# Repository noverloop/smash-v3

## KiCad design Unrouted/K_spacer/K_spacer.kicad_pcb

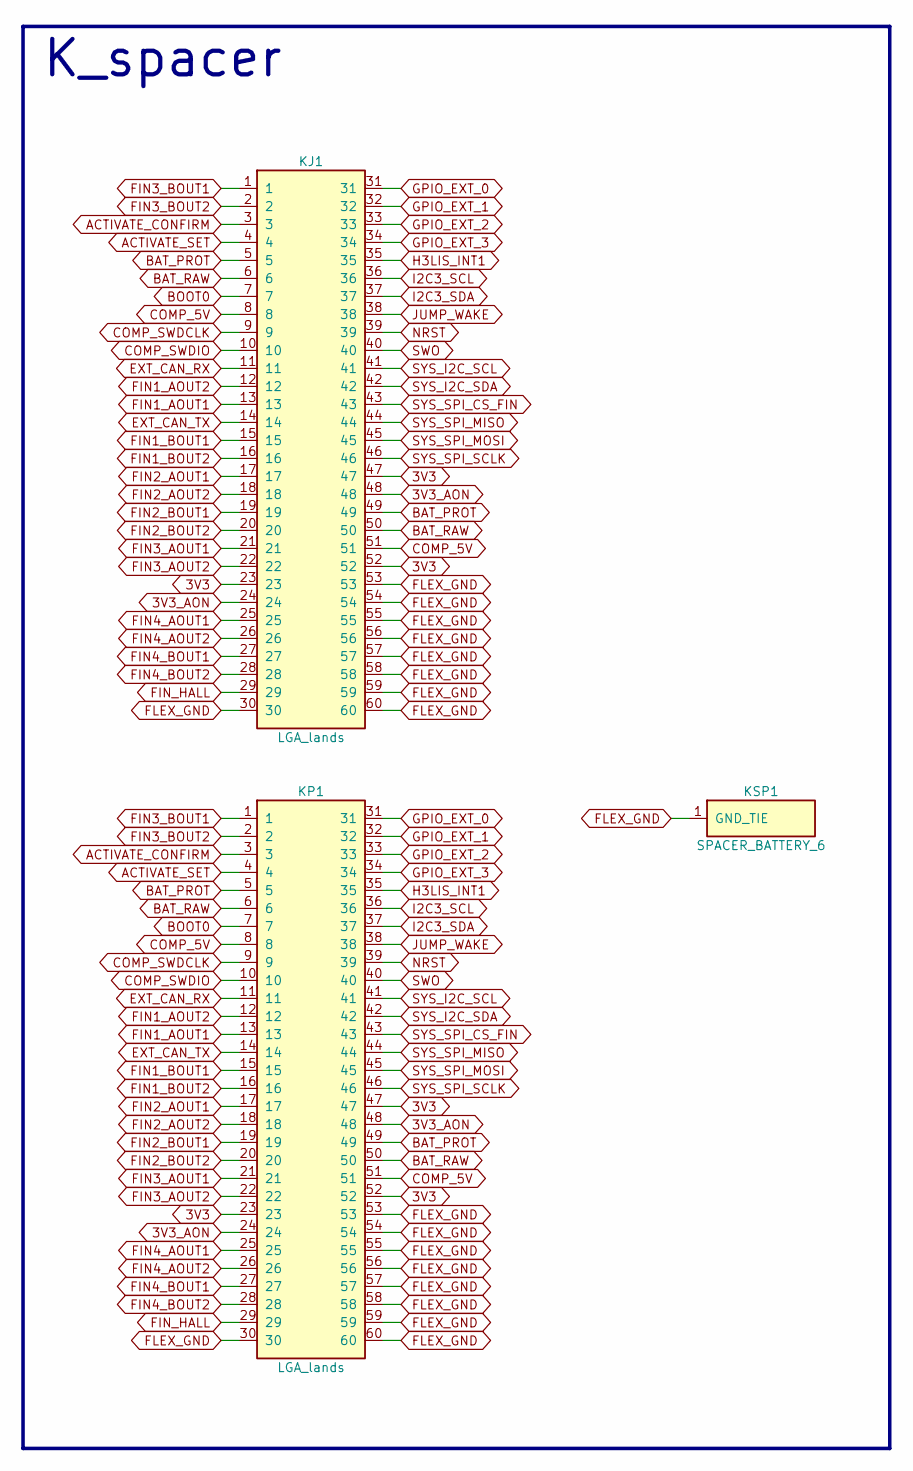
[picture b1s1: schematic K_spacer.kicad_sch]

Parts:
KJ1: LGA_lands; J_spacer_battery_6_top; MPN LGA_lands
KP1: LGA_lands; P_spacer_battery_6_bot; MPN LGA_lands
KSP1: SPACER_BATTERY_6; Spacer_Mechanical_34mm

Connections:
3V3: KJ1.23, KJ1.47, KJ1.52, KP1.23, KP1.47, KP1.52
3V3_AON: KJ1.24, KJ1.48, KP1.24, KP1.48
ACTIVATE_CONFIRM: KJ1.3, KP1.3
ACTIVATE_SET: KJ1.4, KP1.4
BAT_PROT: KJ1.5, KJ1.49, KP1.5, KP1.49
BAT_RAW: KJ1.6, KJ1.50, KP1.6, KP1.50
BOOT0: KJ1.7, KP1.7
COMP_5V: KJ1.8, KJ1.51, KP1.8, KP1.51
COMP_SWDCLK: KJ1.9, KP1.9
COMP_SWDIO: KJ1.10, KP1.10
EXT_CAN_RX: KJ1.11, KP1.11
EXT_CAN_TX: KJ1.14, KP1.14
FIN1_AOUT1: KJ1.13, KP1.13
FIN1_AOUT2: KJ1.12, KP1.12
FIN1_BOUT1: KJ1.15, KP1.15
FIN1_BOUT2: KJ1.16, KP1.16
FIN2_AOUT1: KJ1.17, KP1.17
FIN2_AOUT2: KJ1.18, KP1.18
FIN2_BOUT1: KJ1.19, KP1.19
FIN2_BOUT2: KJ1.20, KP1.20
FIN3_AOUT1: KJ1.21, KP1.21
FIN3_AOUT2: KJ1.22, KP1.22
FIN3_BOUT1: KJ1.1, KP1.1
FIN3_BOUT2: KJ1.2, KP1.2
FIN4_AOUT1: KJ1.25, KP1.25
FIN4_AOUT2: KJ1.26, KP1.26
FIN4_BOUT1: KJ1.27, KP1.27
FIN4_BOUT2: KJ1.28, KP1.28
FIN_HALL: KJ1.29, KP1.29
FLEX_GND: KJ1.30, KJ1.53, KJ1.54, KJ1.55, KJ1.56, KJ1.57, KJ1.58, KJ1.59, KJ1.60, KP1.30, KP1.53, KP1.54, KP1.55, KP1.56, KP1.57, KP1.58, KP1.59, KP1.60, KSP1.1
GPIO_EXT_0: KJ1.31, KP1.31
GPIO_EXT_1: KJ1.32, KP1.32
GPIO_EXT_2: KJ1.33, KP1.33
GPIO_EXT_3: KJ1.34, KP1.34
H3LIS_INT1: KJ1.35, KP1.35
I2C3_SCL: KJ1.36, KP1.36
I2C3_SDA: KJ1.37, KP1.37
JUMP_WAKE: KJ1.38, KP1.38
NRST: KJ1.39, KP1.39
SWO: KJ1.40, KP1.40
SYS_I2C_SCL: KJ1.41, KP1.41
SYS_I2C_SDA: KJ1.42, KP1.42
SYS_SPI_CS_FIN: KJ1.43, KP1.43
SYS_SPI_MISO: KJ1.44, KP1.44
SYS_SPI_MOSI: KJ1.45, KP1.45
SYS_SPI_SCLK: KJ1.46, KP1.46

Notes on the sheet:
K_spacer

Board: 2 copper layers, 4 parts (1 on the bottom side), 46 nets, no tracks yet.

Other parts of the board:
KMH1: smash_mech_potting

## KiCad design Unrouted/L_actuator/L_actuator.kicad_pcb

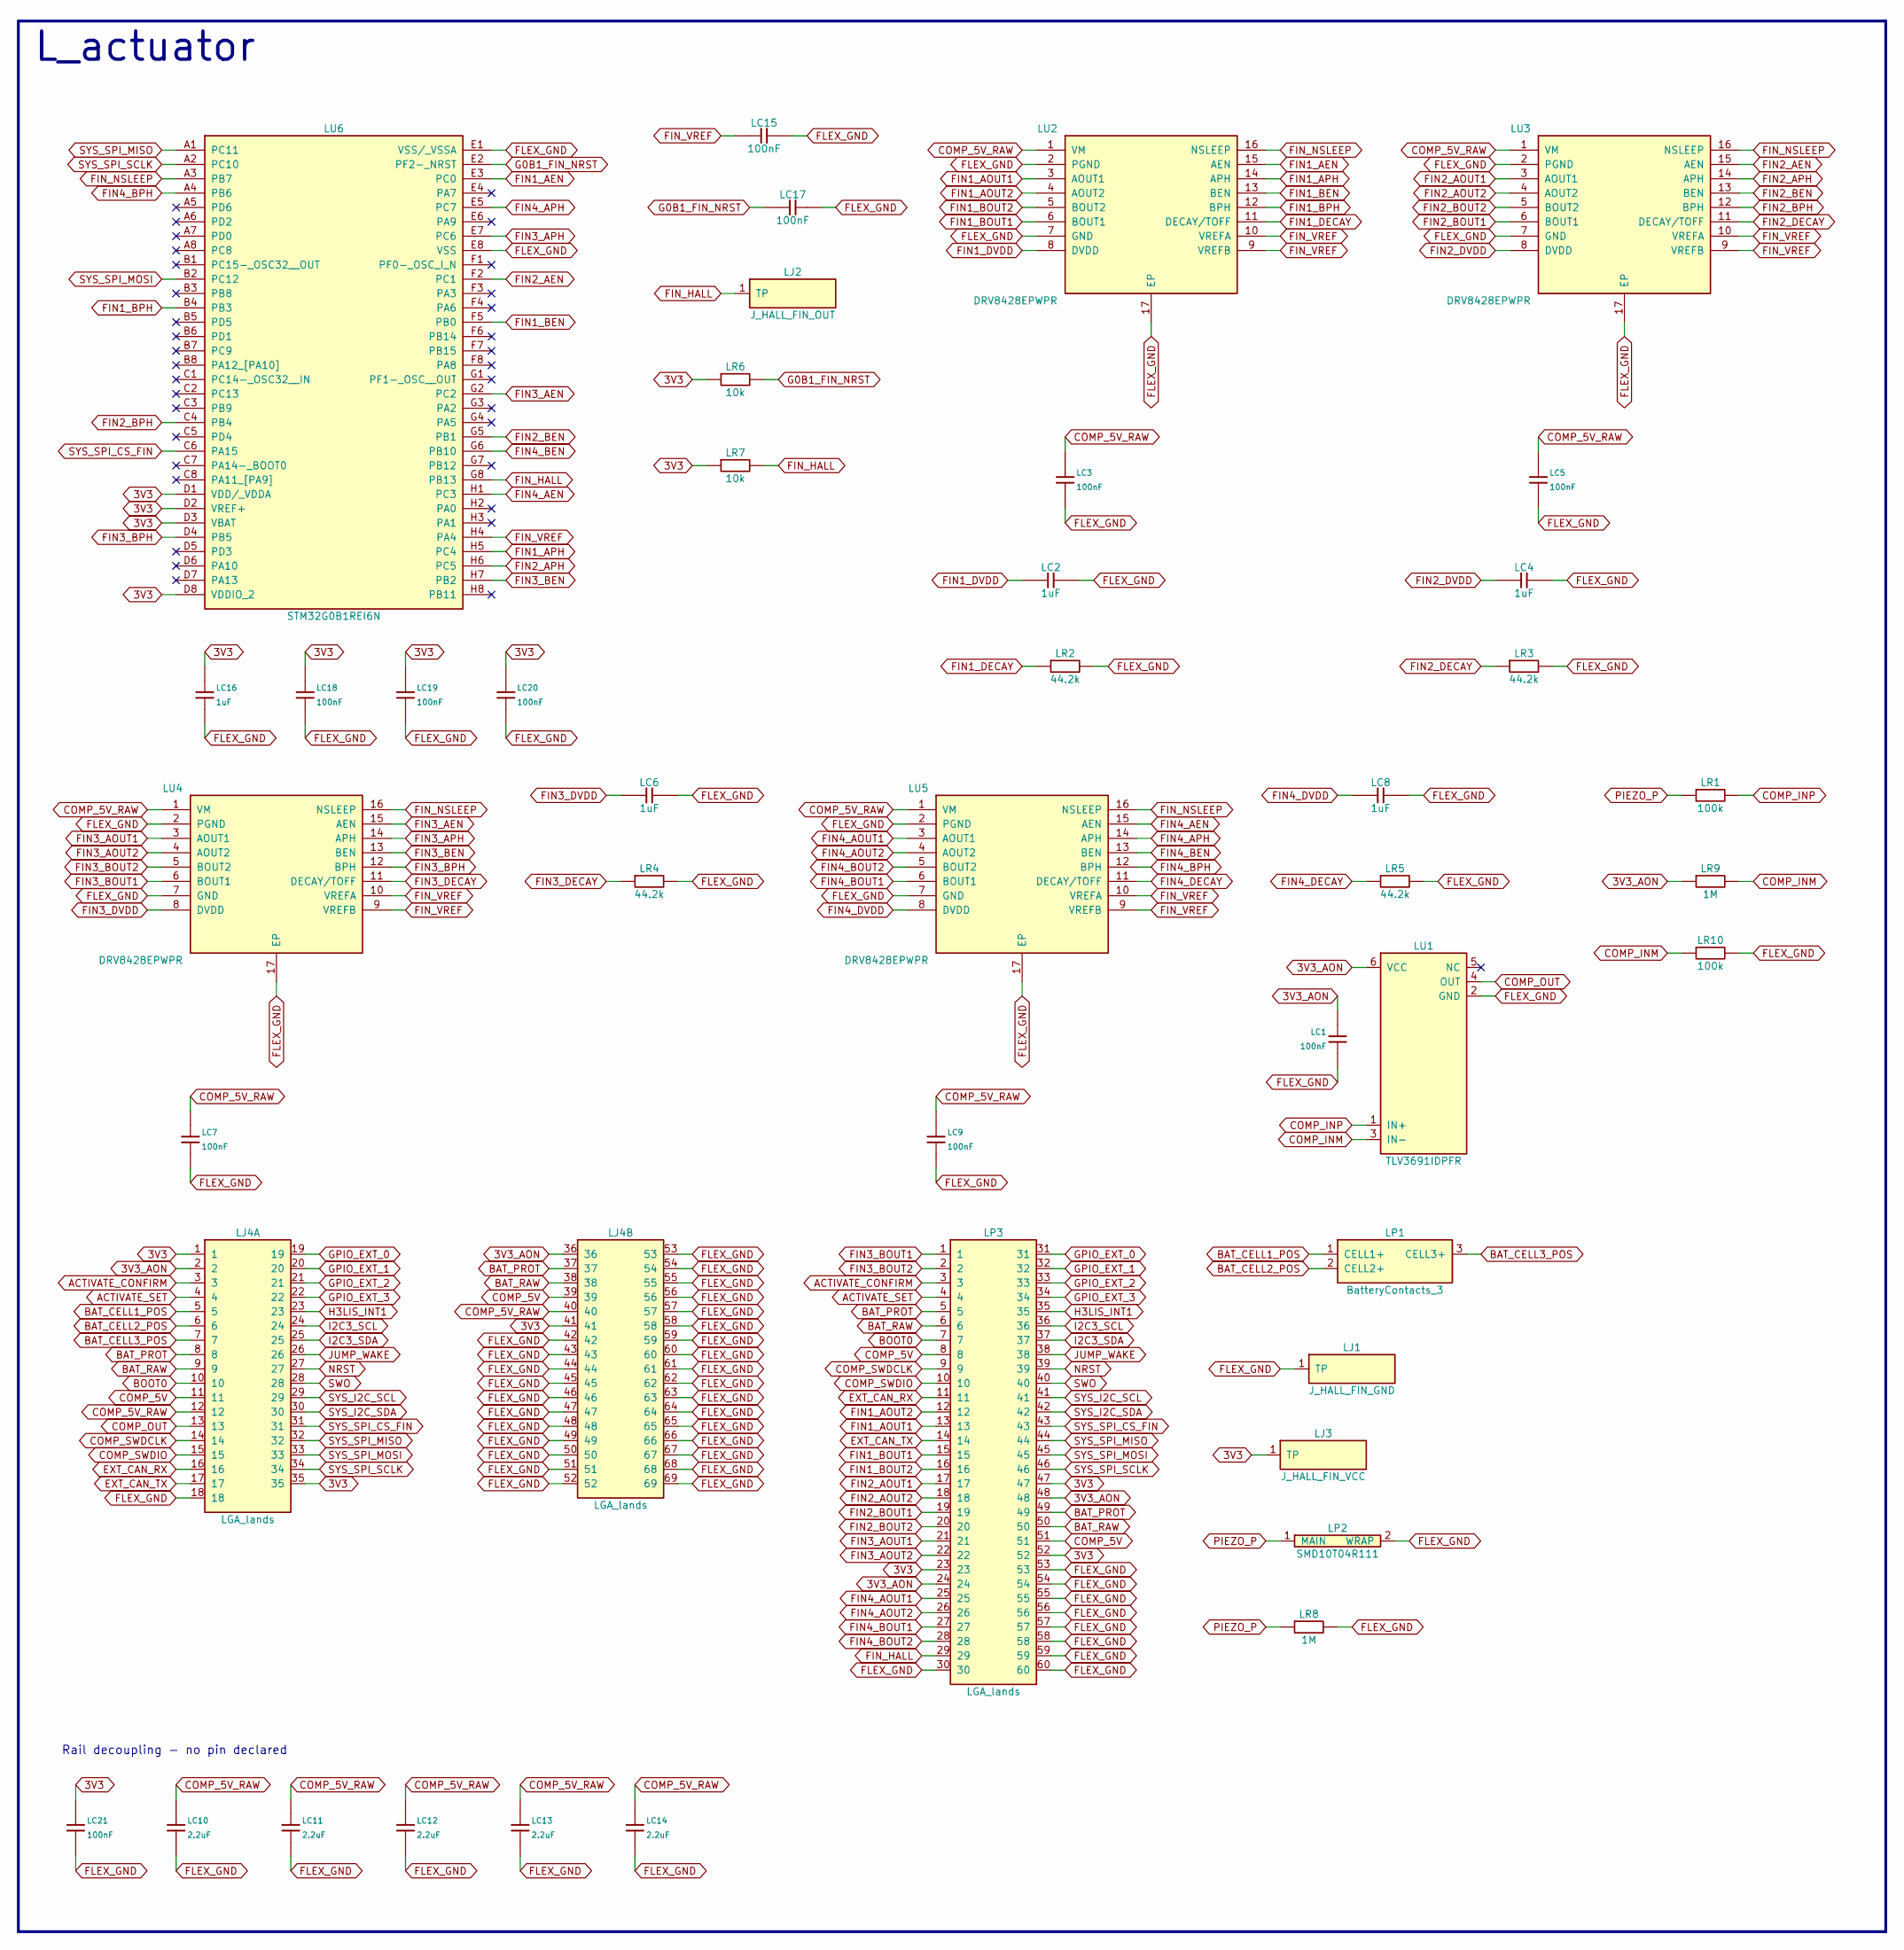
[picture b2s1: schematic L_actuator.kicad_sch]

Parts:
LC1, LC3, LC5, LC7, LC9, LC15, LC17, LC18, LC19, LC20, LC21: 100nF; Capacitor_SMD_C_0402_1005Metric; MPN C0402 X7R 100nF
LC2, LC4, LC6, LC8, LC16: 1uF; Capacitor_SMD_C_0805_2012Metric; MPN C-Series MIL-PRF-32535 X7R 0805 1uF
LC10, LC11, LC12, LC13, LC14: 2.2uF; Capacitor_SMD_C_0603_1608Metric; MPN C-Series MIL-PRF-32535 X7R 0603 2.2uF
LJ1: J_HALL_FIN_GND; Pogo_Pad_D2.0mm
LJ2: J_HALL_FIN_OUT; Pogo_Pad_D2.0mm
LJ3: J_HALL_FIN_VCC; Pogo_Pad_D2.0mm
LJ4: LGA_lands; J_fin_ble_board_spacer_fin_ble_board_wakeup_board; MPN LGA_lands
LP1: BatteryContacts_3; MPN BatteryContacts_3
LP2: SMD10T04R111; PiezoDisc_SMD10T04R111; MPN SMD10T04R111
LP3: LGA_lands; P_fin_ble_board_spacer_battery_6; MPN LGA_lands
LR1, LR10: 100k; Resistor_SMD_R_0402_1005Metric; MPN CRCW0402 100k 1% e3
LR2, LR3, LR4, LR5: 44.2k; Resistor_SMD_R_0402_1005Metric; MPN CRCW0402 44.2k 1% e3
LR6, LR7: 10k; Resistor_SMD_R_0402_1005Metric; MPN CRCW0402 10k 1% e3
LR8, LR9: 1M; Resistor_SMD_R_0402_1005Metric; MPN CRCW0402 1M 1% e3
LU1: TLV3691IDPFR; DPF0006A; MPN TLV3691IDPFR
LU2, LU3, LU4, LU5: DRV8428EPWPR; SOP65P640X120-17N; MPN DRV8428EPWPR
LU6: STM32G0B1REI6N; BGA64C50P8X8_500X500X60; MPN STM32G0B1REI6N

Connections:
3V3: LC16.1, LC18.1, LC19.1, LC20.1, LC21.1, LJ3.1, LJ4.1, LJ4.35, LJ4.41, LP3.23, LP3.47, LP3.52, LR6.1, LR7.1, LU6.D1 (VDD/_VDDA), LU6.D2 (VREF+), LU6.D3 (VBAT), LU6.D8 (VDDIO_2)
3V3_AON: LC1.1, LJ4.2, LJ4.36, LP3.24, LP3.48, LR9.1, LU1.6 (VCC)
ACTIVATE_CONFIRM: LJ4.3, LP3.3
ACTIVATE_SET: LJ4.4, LP3.4
BAT_CELL1_POS: LJ4.5, LP1.1 (CELL1+)
BAT_CELL2_POS: LJ4.6, LP1.2 (CELL2+)
BAT_CELL3_POS: LJ4.7, LP1.3 (CELL3+)
BAT_PROT: LJ4.8, LJ4.37, LP3.5, LP3.49
BAT_RAW: LJ4.9, LJ4.38, LP3.6, LP3.50
BOOT0: LJ4.10, LP3.7
COMP_5V: LJ4.11, LJ4.39, LP3.8, LP3.51
COMP_5V_RAW: LC3.1, LC5.1, LC7.1, LC9.1, LC10.1, LC11.1, LC12.1, LC13.1, LC14.1, LJ4.12, LJ4.40, LU2.1 (VM), LU3.1 (VM), LU4.1 (VM), LU5.1 (VM)
COMP_INM: LR9.2, LR10.1, LU1.3 (IN-)
COMP_INP: LR1.2, LU1.1 (IN+)
COMP_OUT: LJ4.13, LU1.4 (OUT)
COMP_SWDCLK: LJ4.14, LP3.9
COMP_SWDIO: LJ4.15, LP3.10
EXT_CAN_RX: LJ4.16, LP3.11
EXT_CAN_TX: LJ4.17, LP3.14
FIN1_AEN: LU2.15 (AEN), LU6.E3 (PC0)
FIN1_AOUT1: LP3.13, LU2.3 (AOUT1)
FIN1_AOUT2: LP3.12, LU2.4 (AOUT2)
FIN1_APH: LU2.14 (APH), LU6.H5 (PC4)
FIN1_BEN: LU2.13 (BEN), LU6.F5 (PB0)
FIN1_BOUT1: LP3.15, LU2.6 (BOUT1)
FIN1_BOUT2: LP3.16, LU2.5 (BOUT2)
FIN1_BPH: LU2.12 (BPH), LU6.B4 (PB3)
FIN1_DECAY: LR2.1, LU2.11 (DECAY/TOFF)
FIN1_DVDD: LC2.1, LU2.8 (DVDD)
FIN2_AEN: LU3.15 (AEN), LU6.F2 (PC1)
FIN2_AOUT1: LP3.17, LU3.3 (AOUT1)
FIN2_AOUT2: LP3.18, LU3.4 (AOUT2)
FIN2_APH: LU3.14 (APH), LU6.H6 (PC5)
FIN2_BEN: LU3.13 (BEN), LU6.G5 (PB1)
FIN2_BOUT1: LP3.19, LU3.6 (BOUT1)
FIN2_BOUT2: LP3.20, LU3.5 (BOUT2)
FIN2_BPH: LU3.12 (BPH), LU6.C4 (PB4)
FIN2_DECAY: LR3.1, LU3.11 (DECAY/TOFF)
FIN2_DVDD: LC4.1, LU3.8 (DVDD)
FIN3_AEN: LU4.15 (AEN), LU6.G2 (PC2)
FIN3_AOUT1: LP3.21, LU4.3 (AOUT1)
FIN3_AOUT2: LP3.22, LU4.4 (AOUT2)
FIN3_APH: LU4.14 (APH), LU6.E7 (PC6)
FIN3_BEN: LU4.13 (BEN), LU6.H7 (PB2)
FIN3_BOUT1: LP3.1, LU4.6 (BOUT1)
FIN3_BOUT2: LP3.2, LU4.5 (BOUT2)
FIN3_BPH: LU4.12 (BPH), LU6.D4 (PB5)
FIN3_DECAY: LR4.1, LU4.11 (DECAY/TOFF)
FIN3_DVDD: LC6.1, LU4.8 (DVDD)
FIN4_AEN: LU5.15 (AEN), LU6.H1 (PC3)
FIN4_AOUT1: LP3.25, LU5.3 (AOUT1)
FIN4_AOUT2: LP3.26, LU5.4 (AOUT2)
FIN4_APH: LU5.14 (APH), LU6.E5 (PC7)
FIN4_BEN: LU5.13 (BEN), LU6.G6 (PB10)
FIN4_BOUT1: LP3.27, LU5.6 (BOUT1)
FIN4_BOUT2: LP3.28, LU5.5 (BOUT2)
FIN4_BPH: LU5.12 (BPH), LU6.A4 (PB6)
FIN4_DECAY: LR5.1, LU5.11 (DECAY/TOFF)
FIN4_DVDD: LC8.1, LU5.8 (DVDD)
FIN_HALL: LJ2.1, LP3.29, LR7.2, LU6.G8 (PB13)
FIN_NSLEEP: LU2.16 (NSLEEP), LU3.16 (NSLEEP), LU4.16 (NSLEEP), LU5.16 (NSLEEP), LU6.A3 (PB7)
FIN_VREF: LC15.1, LU2.9 (VREFB), LU2.10 (VREFA), LU3.9 (VREFB), LU3.10 (VREFA), LU4.9 (VREFB), LU4.10 (VREFA), LU5.9 (VREFB), LU5.10 (VREFA), LU6.H4 (PA4)
FLEX_GND: LC1.2, LC2.2, LC3.2, LC4.2, LC5.2, LC6.2, LC7.2, LC8.2, LC9.2, LC10.2, LC11.2, LC12.2, LC13.2, LC14.2, LC15.2, LC16.2, LC17.2, LC18.2, LC19.2, LC20.2, LC21.2, LJ1.1, LJ4.18, LJ4.42, LJ4.43, LJ4.44, LJ4.45, LJ4.46, LJ4.47, LJ4.48, LJ4.49, LJ4.50, LJ4.51, LJ4.52, LJ4.53, LJ4.54, LJ4.55, LJ4.56, LJ4.57, LJ4.58, LJ4.59, LJ4.60, LJ4.61, LJ4.62, LJ4.63, LJ4.64, LJ4.65, LJ4.66, LJ4.67, LJ4.68, LJ4.69, LP2.2 (WRAP), LP3.30, LP3.53, LP3.54, LP3.55, LP3.56, LP3.57, LP3.58, LP3.59, LP3.60, LR2.2, LR3.2, LR4.2, LR5.2, LR8.2, LR10.2, LU1.2 (GND), LU2.2 (PGND), LU2.7 (GND), LU2.17 (EP), LU3.2 (PGND), LU3.7 (GND), LU3.17 (EP), LU4.2 (PGND), LU4.7 (GND), LU4.17 (EP), LU5.2 (PGND), LU5.7 (GND), LU5.17 (EP), LU6.E1 (VSS/_VSSA), LU6.E8 (VSS)
G0B1_FIN_NRST: LC17.1, LR6.2, LU6.E2 (PF2-_NRST)
GPIO_EXT_0: LJ4.19, LP3.31
GPIO_EXT_1: LJ4.20, LP3.32
GPIO_EXT_2: LJ4.21, LP3.33
GPIO_EXT_3: LJ4.22, LP3.34
H3LIS_INT1: LJ4.23, LP3.35
I2C3_SCL: LJ4.24, LP3.36
I2C3_SDA: LJ4.25, LP3.37
JUMP_WAKE: LJ4.26, LP3.38
NRST: LJ4.27, LP3.39
PIEZO_P: LP2.1 (MAIN), LR1.1, LR8.1
SWO: LJ4.28, LP3.40
SYS_I2C_SCL: LJ4.29, LP3.41
SYS_I2C_SDA: LJ4.30, LP3.42
SYS_SPI_CS_FIN: LJ4.31, LP3.43, LU6.C6 (PA15)
SYS_SPI_MISO: LJ4.32, LP3.44, LU6.A1 (PC11)
SYS_SPI_MOSI: LJ4.33, LP3.45, LU6.B2 (PC12)
SYS_SPI_SCLK: LJ4.34, LP3.46, LU6.A2 (PC10)

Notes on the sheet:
L_actuator
Rail decoupling - no pin declared

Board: 14 copper layers, 46 parts (31 on the bottom side), 81 nets, no tracks yet.

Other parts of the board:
LMH1, LMH2: smash_mech_potting

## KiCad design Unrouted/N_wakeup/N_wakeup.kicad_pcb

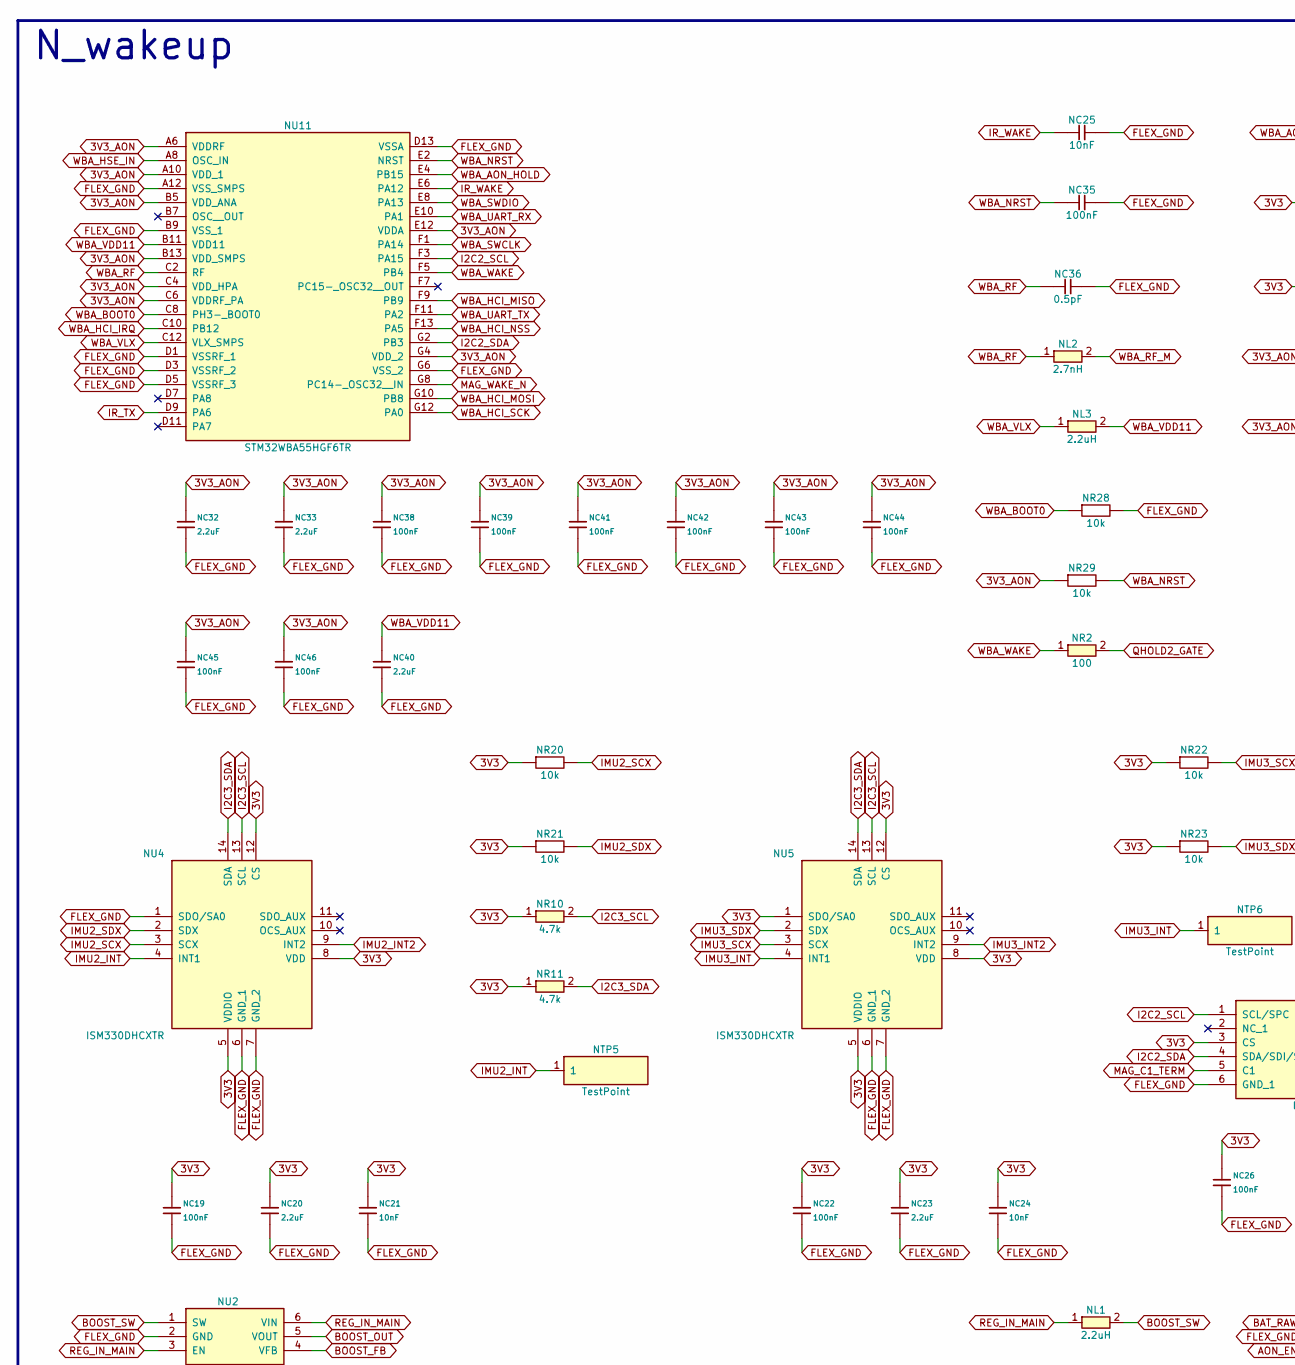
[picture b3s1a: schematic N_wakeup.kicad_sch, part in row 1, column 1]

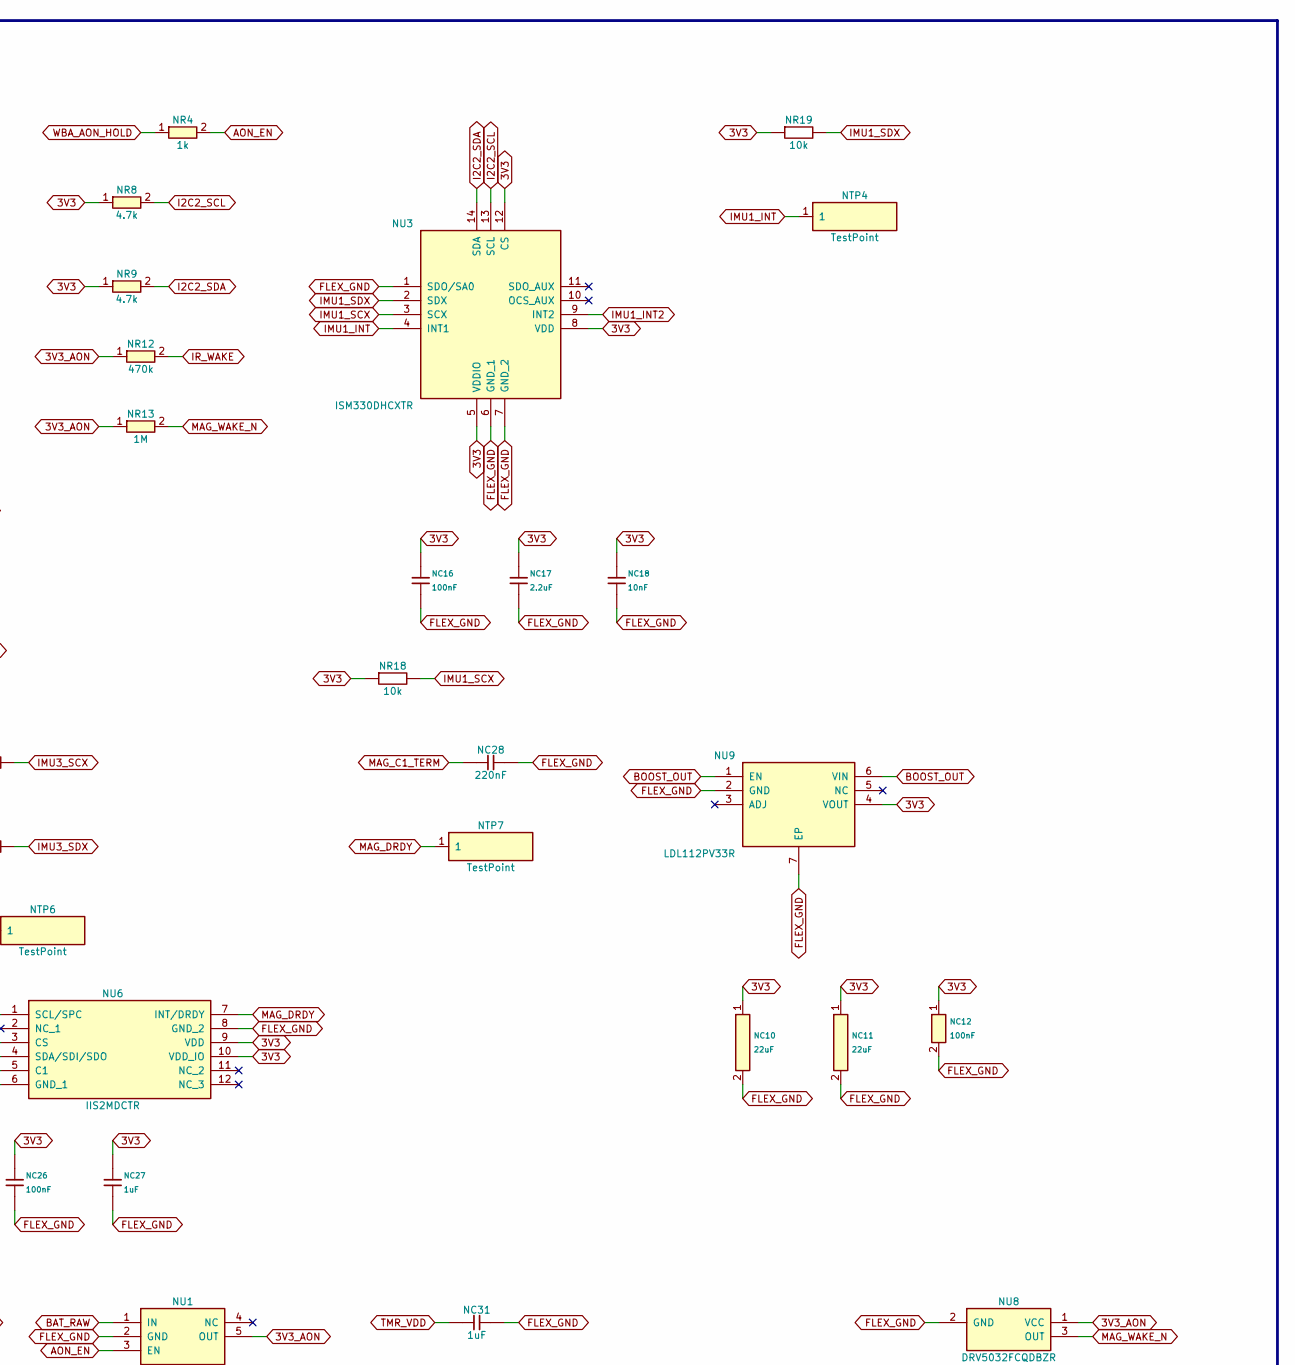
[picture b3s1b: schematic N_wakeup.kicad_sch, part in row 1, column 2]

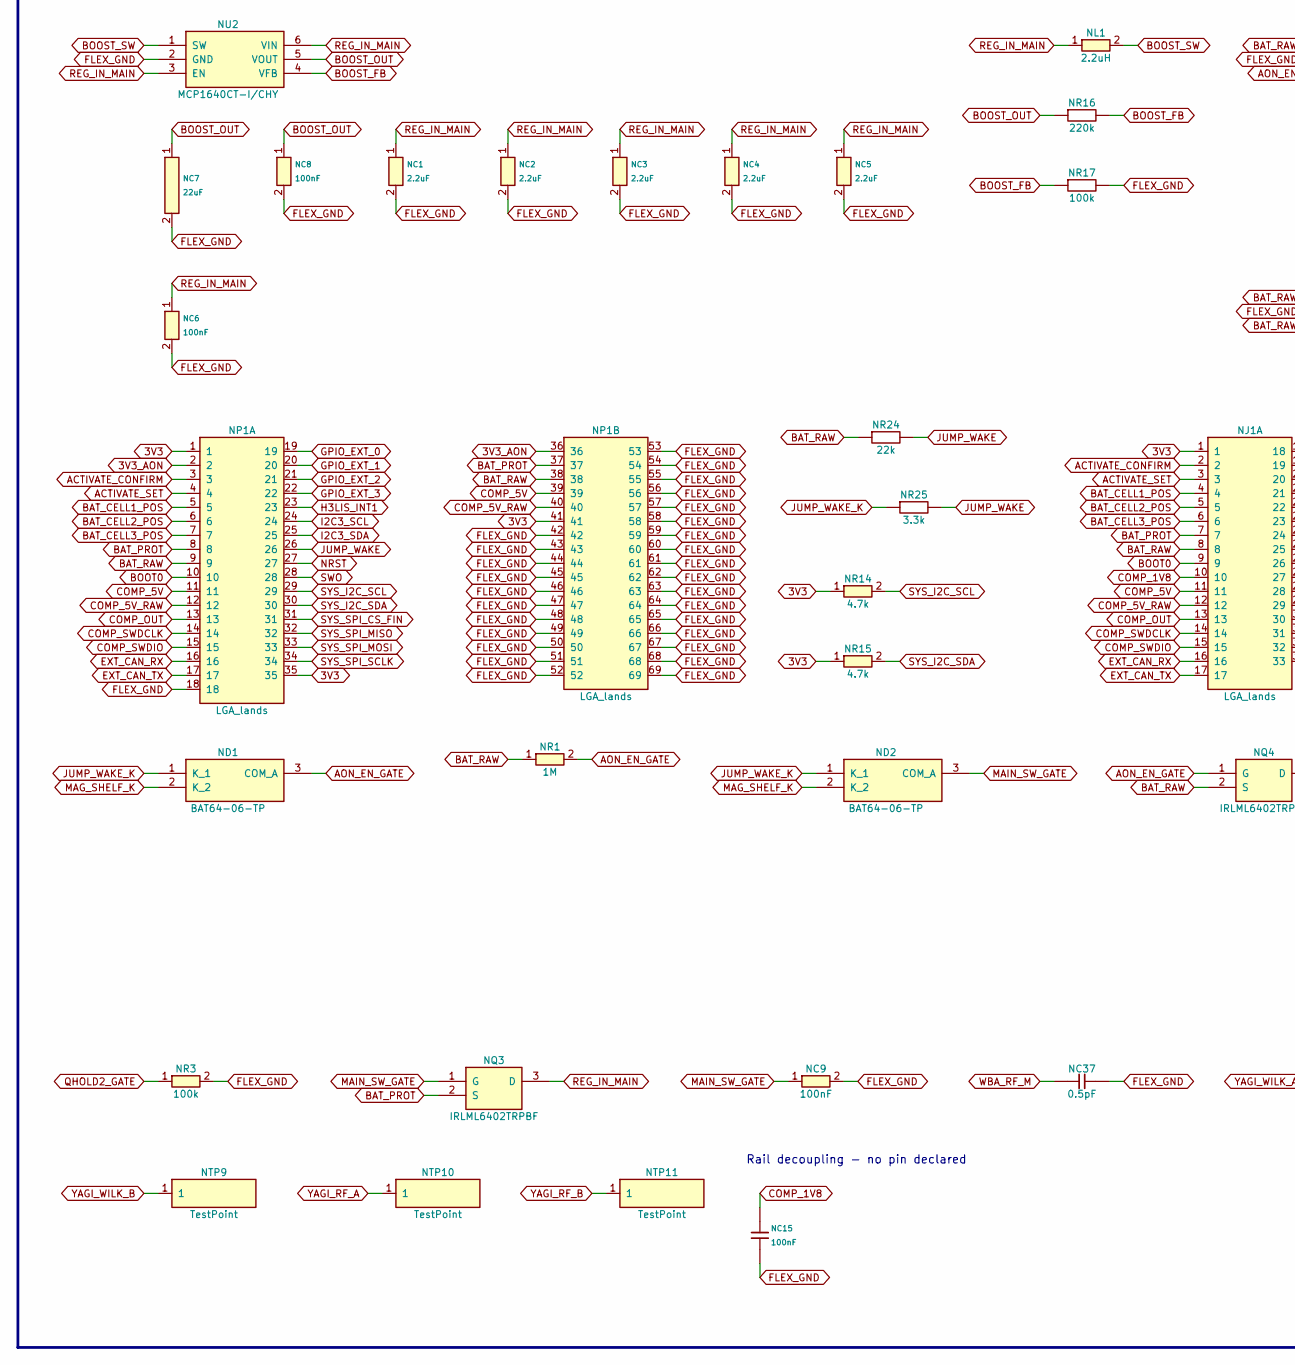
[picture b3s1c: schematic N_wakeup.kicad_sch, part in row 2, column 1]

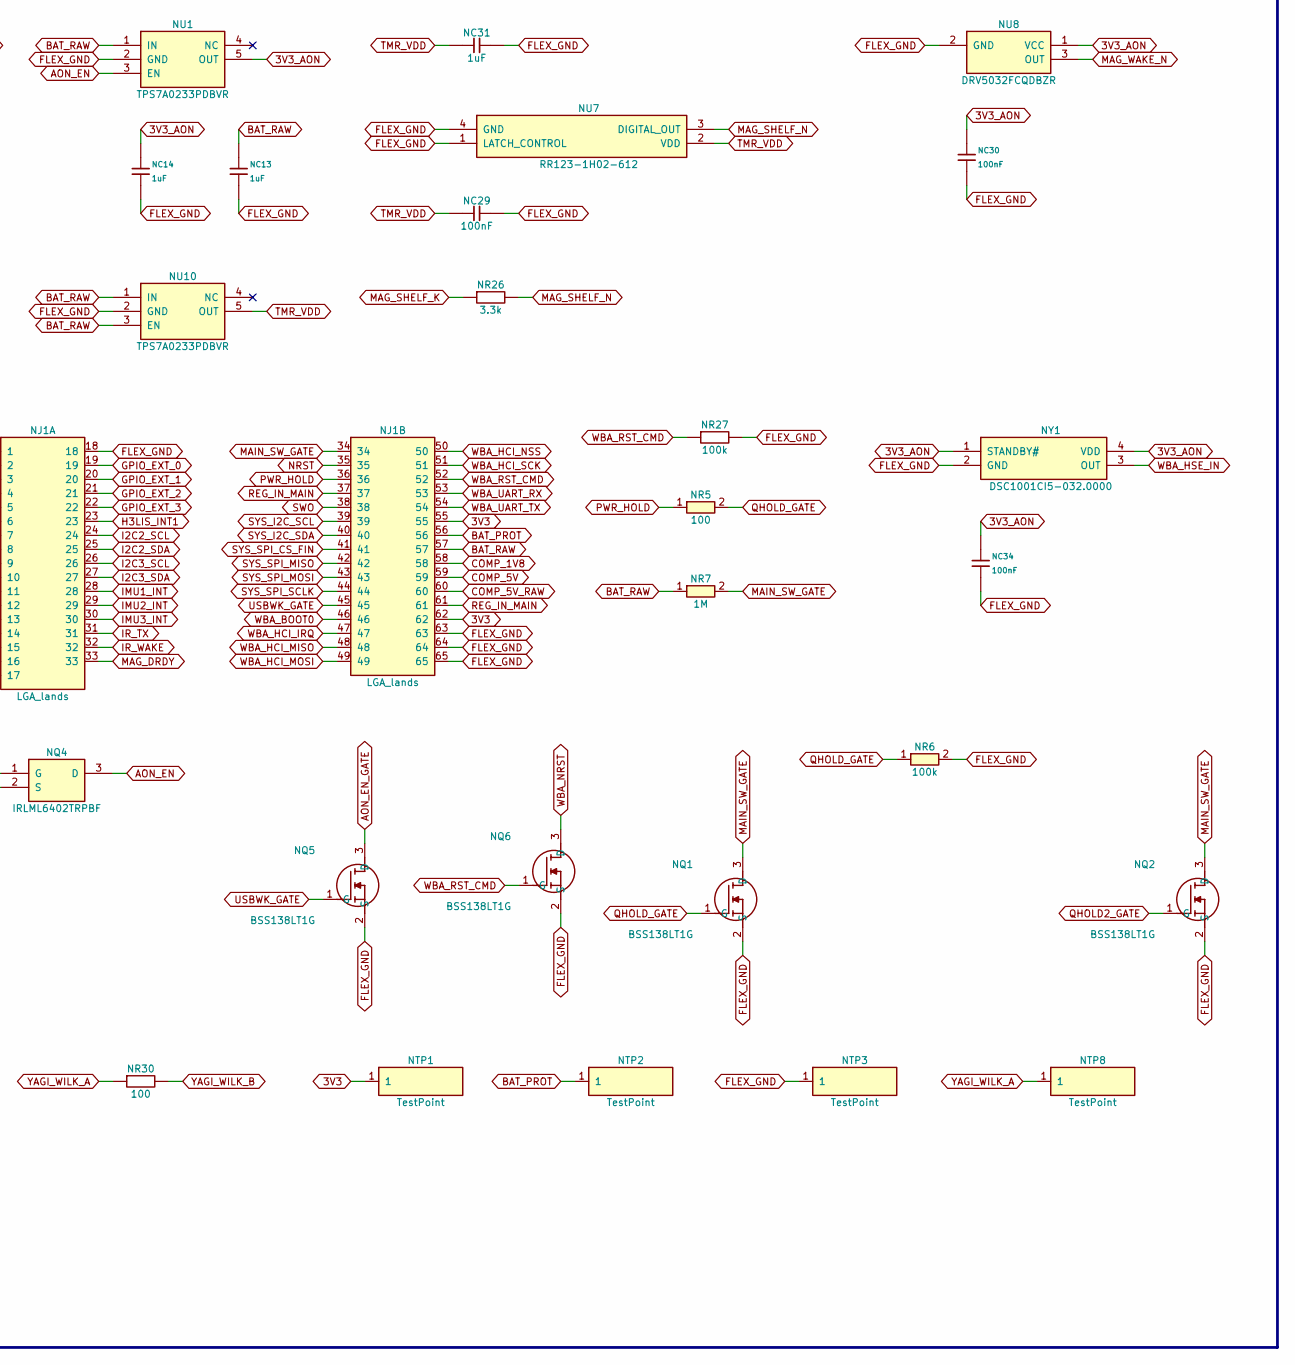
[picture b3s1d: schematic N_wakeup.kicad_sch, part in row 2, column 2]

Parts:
NC1, NC2, NC3, NC4, NC5, NC17, NC20, NC23, NC32, NC33: 2.2uF; Capacitor_SMD_C_0603_1608Metric; MPN C-Series MIL-PRF-32535 X7R 0603 2.2uF
NC6, NC8, NC9, NC12, NC15, NC16, NC19, NC22, NC26, NC29, NC30, NC34, NC35, NC38, NC39, NC41, NC42, NC43, NC44, NC45, NC46: 100nF; Capacitor_SMD_C_0402_1005Metric; MPN C0402 X7R 100nF
NC7, NC10, NC11: 22uF; Capacitor_Tantalum_SMD_CP_EIA-3528-12_Kemet-T; MPN T491T 22uF (3528-12 thinnest variant)
NC13, NC14, NC27, NC31: 1uF; Capacitor_SMD_C_0805_2012Metric; MPN C-Series MIL-PRF-32535 X7R 0805 1uF
NC18, NC21, NC24, NC25: 10nF; Capacitor_SMD_C_0402_1005Metric; MPN C0402 X7R 10nF
NC28: 220nF; Capacitor_SMD_C_0603_1608Metric; MPN C-Series MIL-PRF-32535 X7R 0603 220nF
NC36: 0.5pF; Capacitor_SMD_C_0402_1005Metric; MPN TBD 0402 C0G/NP0 0.5pF (as placed; conf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
NC37: 0.5pF; Capacitor_SMD_C_0603_1608Metric; MPN SQCSVA 0.5pF
NC40: 2.2uF; Capacitor_SMD_C_0402_1005Metric; MPN TBD 0402 X5R 2.2uF (as placed; confirm 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
ND1, ND2: BAT64-06-TP; SOT95P237X125-3N; MPN BAT64-06-TP
NJ1: LGA_lands; J_wakeup_board_spacer_wakeup_board_power_board; MPN LGA_lands
NL1, NL3: 2.2uH; Inductor_SMD_L_2012_2.0x1.25mm; MPN TMS201210ALM-2R2MTAA
NL2: 2.7nH; Inductor_SMD_L_0402_1005Metric; MPN WE-KI 0402 2.7nH (74479xxxxx family)
NP1: LGA_lands; P_wakeup_board_spacer_fin_ble_board_wakeup_board; MPN LGA_lands
NQ1, NQ2, NQ5, NQ6: BSS138LT1G; SOT96P237X111-3N; MPN BSS138LT1G
NQ3, NQ4: IRLML6402TRPBF; SOT95P237X112-3N; MPN IRLML6402TRPBF
NR1, NR7, NR13: 1M; Resistor_SMD_R_0402_1005Metric; MPN CRCW0402 1M 1% e3
NR2, NR5, NR30: 100; Resistor_SMD_R_0402_1005Metric; MPN CRCW0402 100 1% e3
NR3, NR6, NR17, NR27: 100k; Resistor_SMD_R_0402_1005Metric; MPN CRCW0402 100k 1% e3
NR4: 1k; Resistor_SMD_R_0402_1005Metric; MPN CRCW0402 1k 1% e3
NR8, NR9, NR10, NR11, NR14, NR15: 4.7k; Resistor_SMD_R_0402_1005Metric; MPN CRCW0402 4.7k 1% e3
NR12: 470k; Resistor_SMD_R_0402_1005Metric; MPN CRCW0402 470k 1% e3
NR16: 220k; Resistor_SMD_R_0402_1005Metric; MPN CRCW0402 220k 1% e3
NR18, NR19, NR20, NR21, NR22, NR23, NR28, NR29: 10k; Resistor_SMD_R_0402_1005Metric; MPN CRCW0402 10k 1% e3
NR24: 22k; Resistor_SMD_R_0402_1005Metric; MPN CRCW0402 22k 1% e3
NR25, NR26: 3.3k; Resistor_SMD_R_0402_1005Metric; MPN CRCW0402 3.3k 1% e3
NTP1, NTP2, NTP3, NTP4, NTP5, NTP6, NTP7, NTP8, NTP9, NTP10, NTP11: TestPoint; TestPoint_TestPoint_Pad_D1.5mm
NU1, NU10: TPS7A0233PDBVR; SOT95P280X145-5N; MPN TPS7A0233PDBVR
NU2: MCP1640CT-I/CHY; SOT95P270X145-6N; MPN MCP1640CT-I/CHY
NU3, NU4, NU5: ISM330DHCXTR; LSM6DS3USTR (LGA-14); MPN ISM330DHCXTR
NU6: IIS2MDCTR; MPN IIS2MDCTR
NU7: RR123-1H02-612; MPN RR123-1H02-612
NU8: DRV5032FCQDBZR; MPN DRV5032FCQDBZR
NU9: LDL112PV33R; SON95P300X300X100-7N-D; MPN LDL112PV33R
NU11: STM32WBA55HGF6TR; BGA41C35P13X7_298X276X50; MPN STM32WBA55HGF6TR
NY1: DSC1001CI5-032.0000; DSC1001CI50080000; MPN DSC1001CI5-032.0000

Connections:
3V3: NC10.1 (+), NC11.1 (+), NC12.1, NC16.1, NC17.1, NC18.1, NC19.1, NC20.1, NC21.1, NC22.1, NC23.1, NC24.1, NC26.1, NC27.1, NJ1.1, NJ1.55, NJ1.62, NP1.1, NP1.35, NP1.41, NR8.1, NR9.1, NR10.1, NR11.1, NR14.1, NR15.1, NR18.1, NR19.1, NR20.1, NR21.1, NR22.1, NR23.1, NTP1.1, NU3.5 (VDDIO), NU3.8 (VDD), NU3.12 (CS), NU4.5 (VDDIO), NU4.8 (VDD), NU4.12 (CS), NU5.1 (SDO/SA0), NU5.5 (VDDIO), NU5.8 (VDD), NU5.12 (CS), NU6.3 (CS), NU6.9 (VDD), NU6.10 (VDD_IO), NU9.4 (VOUT)
3V3_AON: NC14.1, NC30.1, NC32.1, NC33.1, NC34.1, NC38.1, NC39.1, NC41.1, NC42.1, NC43.1, NC44.1, NC45.1, NC46.1, NP1.2, NP1.36, NR12.1, NR13.1, NR29.1, NU1.5 (OUT), NU8.1 (VCC), NU11.A6 (VDDRF), NU11.A10 (VDD_1), NU11.B5 (VDD_ANA), NU11.B13 (VDD_SMPS), NU11.C4 (VDD_HPA), NU11.C6 (VDDRF_PA), NU11.E12 (VDDA), NU11.G4 (VDD_2), NY1.1 (STANDBY#), NY1.4 (VDD)
ACTIVATE_CONFIRM: NJ1.2, NP1.3
ACTIVATE_SET: NJ1.3, NP1.4
AON_EN: NQ4.3 (D), NR4.2, NU1.3 (EN)
AON_EN_GATE: ND1.3 (COM_A), NQ4.1 (G), NQ5.3 (D), NR1.2
BAT_CELL1_POS: NJ1.4, NP1.5
BAT_CELL2_POS: NJ1.5, NP1.6
BAT_CELL3_POS: NJ1.6, NP1.7
BAT_PROT: NJ1.7, NJ1.56, NP1.8, NP1.37, NQ3.2 (S), NTP2.1
BAT_RAW: NC13.1, NJ1.8, NJ1.57, NP1.9, NP1.38, NQ4.2 (S), NR1.1, NR7.1, NR24.1, NU1.1 (IN), NU10.1 (IN), NU10.3 (EN)
BOOST_FB: NR16.2, NR17.1, NU2.4 (VFB)
BOOST_OUT: NC7.1 (+), NC8.1, NR16.1, NU2.5 (VOUT), NU9.1 (EN), NU9.6 (VIN)
BOOST_SW: NL1.2, NU2.1 (SW)
BOOT0: NJ1.9, NP1.10
COMP_1V8: NC15.1, NJ1.10, NJ1.58
COMP_5V: NJ1.11, NJ1.59, NP1.11, NP1.39
COMP_5V_RAW: NJ1.12, NJ1.60, NP1.12, NP1.40
COMP_OUT: NJ1.13, NP1.13
COMP_SWDCLK: NJ1.14, NP1.14
COMP_SWDIO: NJ1.15, NP1.15
EXT_CAN_RX: NJ1.16, NP1.16
EXT_CAN_TX: NJ1.17, NP1.17
FLEX_GND: NC1.2, NC2.2, NC3.2, NC4.2, NC5.2, NC6.2, NC7.2 (-), NC8.2, NC9.2, NC10.2 (-), NC11.2 (-), NC12.2, NC13.2, NC14.2, NC15.2, NC16.2, NC17.2, NC18.2, NC19.2, NC20.2, NC21.2, NC22.2, NC23.2, NC24.2, NC25.2, NC26.2, NC27.2, NC28.2, NC29.2, NC30.2, NC31.2, NC32.2, NC33.2, NC34.2, NC35.2, NC36.2, NC37.2, NC38.2, NC39.2, NC40.2, NC41.2, NC42.2, NC43.2, NC44.2, NC45.2, NC46.2, NJ1.18, NJ1.63, NJ1.64, NJ1.65, NP1.18, NP1.42, NP1.43, NP1.44, NP1.45, NP1.46, NP1.47, NP1.48, NP1.49, NP1.50, NP1.51, NP1.52, NP1.53, NP1.54, NP1.55, NP1.56, NP1.57, NP1.58, NP1.59, NP1.60, NP1.61, NP1.62, NP1.63, NP1.64, NP1.65, NP1.66, NP1.67, NP1.68, NP1.69, NQ1.2 (S), NQ2.2 (S), NQ5.2 (S), NQ6.2 (S), NR3.2, NR6.2, NR17.2, NR27.2, NR28.2, NTP3.1, NU1.2 (GND), NU2.2 (GND), NU3.1 (SDO/SA0), NU3.6 (GND_1), NU3.7 (GND_2), NU4.1 (SDO/SA0), NU4.6 (GND_1), NU4.7 (GND_2), NU5.6 (GND_1), NU5.7 (GND_2), NU6.6 (GND_1), NU6.8 (GND_2), NU7.1 (LATCH_CONTROL), NU7.4 (GND), NU8.2 (GND), NU9.2 (GND), NU9.7 (EP), NU10.2 (GND), NU11.A12 (VSS_SMPS), NU11.B9 (VSS_1), NU11.D1 (VSSRF_1), NU11.D3 (VSSRF_2), NU11.D5 (VSSRF_3), NU11.D13 (VSSA), NU11.G6 (VSS_2), NY1.2 (GND)
GPIO_EXT_0: NJ1.19, NP1.19
GPIO_EXT_1: NJ1.20, NP1.20
GPIO_EXT_2: NJ1.21, NP1.21
GPIO_EXT_3: NJ1.22, NP1.22
H3LIS_INT1: NJ1.23, NP1.23
I2C2_SCL: NJ1.24, NR8.2, NU3.13 (SCL), NU6.1 (SCL/SPC), NU11.F3 (PA15)
I2C2_SDA: NJ1.25, NR9.2, NU3.14 (SDA), NU6.4 (SDA/SDI/SDO), NU11.G2 (PB3)
I2C3_SCL: NJ1.26, NP1.24, NR10.2, NU4.13 (SCL), NU5.13 (SCL)
I2C3_SDA: NJ1.27, NP1.25, NR11.2, NU4.14 (SDA), NU5.14 (SDA)
IMU1_INT: NJ1.28, NTP4.1, NU3.4 (INT1)
IMU1_INT2: NU3.9 (INT2)
IMU1_SCX: NR18.2, NU3.3 (SCX)
IMU1_SDX: NR19.2, NU3.2 (SDX)
IMU2_INT: NJ1.29, NTP5.1, NU4.4 (INT1)
IMU2_INT2: NU4.9 (INT2)
IMU2_SCX: NR20.2, NU4.3 (SCX)
IMU2_SDX: NR21.2, NU4.2 (SDX)
IMU3_INT: NJ1.30, NTP6.1, NU5.4 (INT1)
IMU3_INT2: NU5.9 (INT2)
IMU3_SCX: NR22.2, NU5.3 (SCX)
IMU3_SDX: NR23.2, NU5.2 (SDX)
IR_TX: NJ1.31, NU11.D9 (PA6)
IR_WAKE: NC25.1, NJ1.32, NR12.2, NU11.E6 (PA12)
JUMP_WAKE: NP1.26, NR24.2, NR25.2
JUMP_WAKE_K: ND1.1 (K_1), ND2.1 (K_1), NR25.1
MAG_C1_TERM: NC28.1, NU6.5 (C1)
MAG_DRDY: NJ1.33, NTP7.1, NU6.7 (INT/DRDY)
MAG_SHELF_K: ND1.2 (K_2), ND2.2 (K_2), NR26.1
MAG_SHELF_N: NR26.2, NU7.3 (DIGITAL_OUT)
MAG_WAKE_N: NR13.2, NU8.3 (OUT), NU11.G8 (PC14-_OSC32__IN)
MAIN_SW_GATE: NC9.1, ND2.3 (COM_A), NJ1.34, NQ1.3 (D), NQ2.3 (D), NQ3.1 (G), NR7.2
NRST: NJ1.35, NP1.27
PWR_HOLD: NJ1.36, NR5.1
QHOLD2_GATE: NQ2.1 (G), NR2.2, NR3.1
QHOLD_GATE: NQ1.1 (G), NR5.2, NR6.1
REG_IN_MAIN: NC1.1, NC2.1, NC3.1, NC4.1, NC5.1, NC6.1, NJ1.37, NJ1.61, NL1.1, NQ3.3 (D), NU2.3 (EN), NU2.6 (VIN)
SWO: NJ1.38, NP1.28
SYS_I2C_SCL: NJ1.39, NP1.29, NR14.2
SYS_I2C_SDA: NJ1.40, NP1.30, NR15.2
SYS_SPI_CS_FIN: NJ1.41, NP1.31
SYS_SPI_MISO: NJ1.42, NP1.32
SYS_SPI_MOSI: NJ1.43, NP1.33
SYS_SPI_SCLK: NJ1.44, NP1.34
TMR_VDD: NC29.1, NC31.1, NU7.2 (VDD), NU10.5 (OUT)
USBWK_GATE: NJ1.45, NQ5.1 (G)
WBA_AON_HOLD: NR4.1, NU11.E4 (PB15)
WBA_BOOT0: NJ1.46, NR28.1, NU11.C8 (PH3-_BOOT0)
WBA_HCI_IRQ: NJ1.47, NU11.C10 (PB12)
WBA_HCI_MISO: NJ1.48, NU11.F9 (PB9)
WBA_HCI_MOSI: NJ1.49, NU11.G10 (PB8)
WBA_HCI_NSS: NJ1.50, NU11.F13 (PA5)
WBA_HCI_SCK: NJ1.51, NU11.G12 (PA0)
WBA_HSE_IN: NU11.A8 (OSC_IN), NY1.3 (OUT)
WBA_NRST: NC35.1, NQ6.3 (D), NR29.2, NU11.E2 (NRST)
WBA_RF: NC36.1, NL2.1, NU11.C2 (RF)
WBA_RF_M: NC37.1, NL2.2
WBA_RST_CMD: NJ1.52, NQ6.1 (G), NR27.1
WBA_SWCLK: NU11.F1 (PA14)
WBA_SWDIO: NU11.E8 (PA13)
WBA_UART_RX: NJ1.53, NU11.E10 (PA1)
WBA_UART_TX: NJ1.54, NU11.F11 (PA2)
WBA_VDD11: NC40.1, NL3.2, NU11.B11 (VDD11)
WBA_VLX: NL3.1, NU11.C12 (VLX_SMPS)
WBA_WAKE: NR2.1, NU11.F5 (PB4)
YAGI_RF_A: NTP10.1
YAGI_RF_B: NTP11.1
YAGI_WILK_A: NR30.1, NTP8.1
YAGI_WILK_B: NR30.2, NTP9.1

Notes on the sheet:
N_wakeup
Rail decoupling - no pin declared

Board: 14 copper layers, 114 parts (80 on the bottom side), 85 nets, no tracks yet.

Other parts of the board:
NMH1, NMH2: smash_mech_potting
